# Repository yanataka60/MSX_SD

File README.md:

# MSXにSD-CARDからロード、セーブ機能

　MSX、MSX2、MSX2+、MSXturboRでSD-CARDからロード、セーブ機能を実現するものです。

　ROM-BASIC、DISK-BASICのどちらからも使えますが、DISK-BASICのフリーエリアでは動かないカセット用プログラム(ゲーム)もあります。

　FDD内蔵機種でフリーエリアが足りない場合は、SHIFTキーを押しながら電源投入又はリセットしてFDDを切り離してください。

　CMTからの読み込み実行に数分掛かっていたゲームも数十秒で実行できます。

　なお、Arduino、ROMへ書き込むための機器が別途必要となります。

## 対応できないもの
　BASICにSD専用命令を追加することでSD-CARDへのアクセスを実現しています。

　機械語からBIOSをコール、又は独自ルーチンでCMTからLOADするソフトには対応していません。

　雑誌打ち込み系のLOAD、SAVEを想定しています。市販ソフトはLOAD出来ればラッキーくらいに思って活用してください。

## 参考
　市販ソフトをcasファイル化した時に多段ロードではない単純にBASICプログラム、機械語プログラムをロードするものは大丈夫だと思います。

　また、２段ロードでも最初のBASICプログラム中から2段目の機械語プログラムを「BLOAD」で呼び出すものは「CALL SBLOAD」又は「CALL SBLOAD(,R)」に置き換えることで対応できると思います。

## 回路図
　KiCadフォルダ内のMSX_SD.pdfを参照してください。

[回路図](https://github.com/yanataka60/MSX_SD/blob/main/Kicad/MSX_SD.pdf)

## 部品
|番号|品名|数量|備考|
| ------------ | ------------ | ------------ | ------------ |
||J2、J3のいずれか(注1)|||
|J2|Micro_SD_Card_Kit|1|秋月電子通商 AE-microSD-LLCNV (注2)|
|J3|MicroSD Card Adapter|1|Arduino等に使われる5V電源に対応したもの (注4)|
|D1|1N4148|1||
|U1|74LS02|1||
|U2|74LS138|1||
|U3|27256相当品|1|29C256は可、28C256は不可|
|U4|8255|1||
|U5|Arduino_Pro_Mini_5V|1|Atmega328版を使用 168版は不可。(注3)|
|C1～C4|積層セラミックコンデンサ 0.1uF|4||
|C5|電解コンデンサ 16v100uF|1||
||ピンヘッダ|2Pin分|Arduino_Pro_MiniにはA4、A5用のピンヘッダが付いていないため別途調達が必要です 秋月電子通商 PH-1x40SGなど|
||ピンソケット(任意)|26Pin分|Arduino_Pro_Miniを取り外し可能としたい場合に調達します 秋月電子通商 FHU-1x42SGなど|

　　　注1)J2又はJ3のどちらかを選択して取り付けてください。

　　　注2)秋月電子通商　AE-microSD-LLCNVのJ1ジャンパはショートしてください。

　　　注3)Arduino Pro MiniはA4、A5ピンも使っています。

　　　注4)MicroSD Card Adapterを使う場合

　　　　　J3に取り付けます。

　　　　　MicroSD Card Adapterについているピンヘッダを除去してハンダ付けするのが一番確実ですが、J3の穴にMicroSD Card Adapterをぴったりと押しつけ、裏から多めにハンダを流し込むことでハンダ付けをする方法もあります。なお、この方法の時にはしっかりハンダ付けが出来たかテスターで導通を確認しておいた方が安心です。

## ROMへの書込み
　Z80フォルダ内のEXT_ROM.binをROMライター(TL866II Plus等)を使って27256又は29C256に書き込みます。

## Arduinoプログラム
　Arduino IDEを使ってArduinoフォルダのMSX_SDフォルダ内MSX_SD.inoを書き込みます。

　SdFatライブラリを使用しているのでArduino IDEメニューのライブラリの管理からライブラリマネージャを立ち上げて「SdFat」をインストールしてください。

　「SdFat」で検索すれば見つかります。「SdFat」と「SdFat - Adafruit Fork」が見つかりますが「SdFat」のほうを使っています。

## 接続
　カートリッジスロットに挿入します。

### SD-CARD
　出来れば8GB以下のSDカードを用意してください。

　ArduinoのSdFatライブラリは、SD規格(最大2GB)、SDHC規格(2GB～32GB)に対応していますが、SDXC規格(32GB～2TB)には対応していません。

　また、SDHC規格のSDカードであっても32GB、16GBは相性により動作しないものがあるようです。

　FAT16又はFAT32が認識できます。NTFSは認識できません。

　ルートに置かれた拡張子が「.CAS」形式ファイルのみ認識できます。(以外のファイル、フォルダも表示されますがLOAD実行の対象になりません)

　ファイル名は拡張子を除いて32文字まで、ただし半角カタカナ、及び一部の記号はArduinoが認識しないので使えません。パソコンでファイル名を付けるときはアルファベット、数字および空白でファイル名をつけてください。

## 使い方
　BASICから以下のコマンドが使えます。

　各コマンドでパラメータを指定する場合には必ず"("をつけてください。"("が無い場合には、MSXの仕様により入力した文字列のすべてがコマンド名として解釈されるため、パラメータを指定しなかったことになります。

### ○CALL SDIR[CR] 又は CALL SDIR("文字列")[CR]
### 【省略形】_SDIR[CR] 又は _SDIR("文字列")[CR]

文字列を指定するときは必ず"("をつけてください。後ろの")"は有っても無くても構いません。

ダブルコーテーションは有っても無くても構いません。

文字列を入力せずにSDIR[CR]のみ入力するとSD-CARDルートディレクトリにあるファイルの一覧を表示します。

文字列を付けて入力すればSD-CARDルートディレクトリにあるその文字列から始まるファイルの一覧を表示します。

10件表示したところで指示待ちになるので打ち切るならESCを入力すると打ち切られ、Bキーで前の10件に戻ります。それ以外のキーで次の10件を表示します。

　行頭に0から9の数字を付加して表示してあるのでSETLしたいファイルの頭についている数字を入力するとSETLコマンドが実行されます。

　表示される順番は、登録順となりファイル名アルファベッド順などのソートした順で表示することはできません。

#### 例)
　　CALL SDIR[CR]

　　CALL SDIR("P")[CR]

　　CALL SDIR(P)[CR]

### ○CALL SETL("DOSファイル名")[CR]
### 【省略形】_SETL("DOSファイル名")[CR]
指定したDOSファイル名のファイルをSD-CARDからLOAD出来るようにセットします。ファイル名の前には必ず"("をつけてください。後ろの")"は有っても無くても構いません。

ダブルコーテーションは有っても無くても構いません。

ファイル名の最後の「.cas」は有っても無くても構いません。

SETLを実行することでカセットテープをセットして読み込む準備をしたことになります。

#### 例)
　　CALL SETL("TEST")[CR]

### ○CALL SLOAD[CR] 又は CALL SLOAD("ファイル名")[CR]
### 【省略形】_SLOAD[CR] 又は _SLOAD("ファイル名")[CR]
CALL SDIR又はCALL SETLでセットしたDOSファイル名に記録されているBASICプログラムをロードします。

ファイル名の前には必ず"("をつけてください。

ダブルコーテーションは有っても無くても構いません。

ファイルデスクリプタ「CAS0:」は不要です。

ASCII形式のBASICプログラムには対応していません。

Rオプションには対応していません。LOAD後実行したい場合にはマルチステートメントでRUNを付け加え、CALL SLOAD:RUN[CR]又はCALL SLOAD("ファイル名"):RUN[CR]などとしてください。

ファイル名が指定されていなければ最初に見つけたBASICプログラムから、ファイル名を指定していれば入力したファイル名から始まるBASICプログラムが見つかるとロードが始まります。

#### 例)
　　CALL SLOAD[CR]

　　CALL SLOAD("TEST")[CR]

カセットテープと同じようにSLOAD命令等で読み込みが行われる度にDOSファイル名で指定したファイルに保存されているプログラムが先頭から一つずつ読み込まれます。

カセットデッキのように巻き戻しは無いので戻りたい時にはもう一度CALL SDIR又はCALL SETLコマンドを実行すれば先頭のプログラム又はデータに戻ります。

### ○CALL SBLOAD[CR]、CALL SBLOAD ("ファイル名")[CR]、CALL SBLOAD(,R)[CR] 又は CALL SBLOAD ("ファイル名",R)[CR]
### 【省略形】_SBLOAD[CR]、_SBLOAD ("ファイル名")[CR]、_SBLOAD(,R)[CR] 又は _SBLOAD ("ファイル名",R)[CR]
CALL SDIR又はCALL SETLでセットしたDOSファイル名に記録されている機械語プログラムをロードします。

ファイル名の前には必ず"("をつけてください。

ダブルコーテーションは有っても無くても構いません。

ファイルデスクリプタ「CAS0:」は不要です。

RオプションをつけることでLOAD後指定された実行開始アドレスから直ちに実行されます。

ファイル名が指定されていなければ最初に見つけた機械語プログラムから、ファイル名を指定していれば入力したファイル名から始まる機械語プログラムが見つかるとロードが始まります。

#### 例)
　　CALL SBLOAD[CR]

　　CALL SBLOAD("TEST")[CR]

　　CALL SBLOAD(,R)[CR]

　　CALL SBLOAD("TEST",R)[CR]

カセットテープと同じようにSBLOAD命令等で読み込みが行われる度にDOSファイル名で指定したファイルに保存されているプログラムが先頭から一つずつ読み込まれます。

カセットデッキのように巻き戻しは無いので戻りたい時にはもう一度CALL SDIR又はCALL SETLコマンドを実行すれば先頭のプログラム又はデータに戻ります。

### ○CALL SETS("DOSファイル名")[CR]
### 【省略形】_SETS("DOSファイル名")[CR]
SD-CARDへのSAVEが指定したDOSファイル名のファイルとなるようにセットします。ファイル名の前には必ず"("をつけてください。後ろの")"は有っても無くても構いません。

ダブルコーテーションは有っても無くても構いません。

ファイル名の最後の「.cas」は有っても無くても構いません。

指定したDOSファイル名のファイルがSD-CARDに存在しない場合は新たに作成され、存在する場合にはそのファイルの続きに追記されます。

SETSを実行することでカセットテープをセットして書き込む準備をしたことになります。

なお、SETSを実行せずにSSAVE、SBSAVEコマンドを実行すると「DEFAULT.cas」というDOSファイル名のファイルに自動的に書き込まれます。

「DEFAULT.cas」でなく好きなDOSファイル名のファイルに書き込みたい時には事前にSETSコマンドを実行してください。

#### 例)
　　CALL SETS("TEST")[CR]

### ○CALL SSAVE("ファイル名")[CR]
### 【省略形】_SSAVE("ファイル名")[CR]
CALL SETSでセットしたDOSファイル名のファイルにBASICプログラムをSAVEします。

ファイル名の前には必ず"("をつけてください。

ダブルコーテーションで必ず括る必要はありませんが、MSXの仕様上ダブルコーテーションで括った場合には文字列として判断され小文字はそのまま小文字ですが、括らなかった場合には変数名と判断され小文字はすべて大文字に変換されます。

ファイルデスクリプタ「CAS0:」は不要です。

ファイル名は省略できません。6文字以内でファイル名を指定してください。

#### 例)
　　CALL SSAVE("test")[CR]　　　:ファイル名testとしてSAVEされます。

　　CALL SSAVE("TEST")[CR]　　　:ファイル名TESTとしてSAVEされます。

　　CALL SSAVE(test)[CR]　　　　:ファイル名TESTとしてSAVEされます。

　　CALL SSAVE(TEST)[CR]　　　　:ファイル名TESTとしてSAVEされます。

カセットテープと同じようにSSAVE命令等で書き込みが行われる度にDOSファイル名で指定したファイルにBASICプログラムを追記します。

### ○CALL SBSAVE("ファイル名",開始アドレス,終了アドレス,実行開始アドレス)[CR]
### 【省略形】_SBSAVE("ファイル名",開始アドレス,終了アドレス,実行開始アドレス)[CR]
CALL SETSでセットしたDOSファイル名のファイルに開始アドレスから終了アドレスまでのメモリ上に置かれている機械語プログラムをSAVEします。

ファイル名の前には必ず"("をつけてください。

ダブルコーテーションで必ず括る必要はありませんが、MSXの仕様上ダブルコーテーションで括った場合には文字列として判断され小文字はそのまま小文字ですが、括らなかった場合には変数名と判断され小文字はすべて大文字に変換されます。

ファイルデスクリプタ「CAS0:」は不要です。

ファイル名、開始アドレス、終了アドレス、実行開始アドレスは16進数(&H)または32767までの10進数で指定してください。省略できません。

6文字以内でファイル名を指定してください。

#### 例)
　　CALL SBSAVE("TEST",&HA000,&HAFFF,&HA000)[CR]

カセットテープと同じようにSBSAVE命令等で書き込みが行われる度にDOSファイル名で指定したファイルに機械語プログラムを追記します。

### ○CALL DUMP[CR] 又は CALL DUMP(開始アドレス)[CR]
### 【省略形】_DUMP[CR] 又は _DUMP(開始アドレス)[CR]
メモリの内容を開始アドレスから128Byte分表示します。

開始アドレスを指定する場合には"("をつけ、16進数(&H)または32767までの10進数で指定してください。

開始アドレスを省略した場合には直前にCALL SBLOADされた機械語プログラムの実行開始アドレス又はCALL DUMPで表示された続きを表示します。

#### 例)
　　CALL DUMP(&HA000)[CR]　　　:アドレスA000からメモリ内容を表示します。

　　直後にCALL DUMP[CR]　　　　:直前に表示したメモリ内容(&HA000～&HA07F)の続きとして&HA080～&HA0FFを表示します。

　　CALL SBLOADを実行した直後にCALL DUMP[CR]　　　　:直前にLOADされた機械語プログラムの実行開始アドレスからメモリ内容を表示します。

### ○CALL EDIT[CR] 又は CALL EDIT(開始アドレス)[CR]
### 【省略形】_EDIT[CR] 又は _EDIT(開始アドレス)[CR]
開始アドレスが表示されるのでその後ろに16進数を入力し最後に[CR]を押すことでメモリにデータを書き込むことができます。

開始アドレスを指定する場合には"("をつけ、16進数(&H)または32767までの10進数で指定してください。

開始アドレスを省略した場合には直前にCALL SBLOADされた機械語プログラムの実行開始アドレス又はCALL DUMPで表示された続きのアドレスが書き込み開始アドレスとなります。

#### 例)
　　CALL EDIT(&HA000)[CR]　　　:とすると改行してA000が表示されるので16進数を入力後[CR]を押す。

　　A000 12 34 56 78 90[CR]　　:アドレスA000から 12 34 56 78 90の5Byteが書き込まれ、次のアドレスA005が表示される。

　　A005 [CR]　　　　　　　　　:終了したい時はアドレス表示の後に[CR]だけ押せば終了となる。

### ○CALL GOTO[CR] 又は CALL GOTO(実行開始アドレス)[CR]
### 【省略形】_GOTO[CR] 又は _GOTO(実行開始アドレス)[CR]
実行開始アドレスの機械語プログラムを呼び出します。

開始アドレスを指定する場合には"("をつけ、16進数(&H)または32767までの10進数で指定してください。

開始アドレスを省略した場合には直前にCALL SBLOADされた機械語プログラムの実行開始アドレス又はCALL DUMPで表示された続きが実行開始アドレスとなります。

#### 例)
　　CALL GOTO(&HA000)[CR]　　　:アドレスA000からの機械語プログラムを呼び出します。

　　CALL SBLOADを実行した直後にCALL GOTO[CR]　　　:直前にLOADされた機械語プログラムの実行開始アドレスの機械語プログラムを呼び出します。CALL SBLOAD(,R)と同等の動作となります。

### 操作上の注意
　~~「SD-CARD INITIALIZE ERROR」と表示されたときは、SD-CARDが挿入されているか確認し、SD-CARDを挿入して再度実行してください。~~

　~~SD-CARDにアクセスしていない時に電源が入ったままで SD-CARDを抜いた後、再挿入しても動作します。もし、「SD-CARD INITIALIZE ERROR」となる場合には本体の電源を入れ直してください。~~

　(2024.3.13) SD-CARDにアクセスしていない時に電源が入ったままでSD-CARDを抜くと再度SD-CARDを挿入してもSD-CARDにアクセスできない問題を解消しました。(Arduinoを最新版に書き換えてください)

　再度SD-CARDを挿入した後、_SDIR、_SETL、_SETS、_SSAVE、_SBSAVE等でSD-CARDに3回ほどアクセスすれば復旧します。

　_SLOAD、_SBLOADでも復旧しますが、_SDIR、_SETL等DOSファイル名をセットするところから復旧させることをお勧めします。

## 機械語多段ロードでBIOSをコールしているプログラムへの対応【テストバージョン】
　「MSX快速マシン語ゲーム集」に掲載されている「ジグソーセット」は、選んだ絵のデータを機械語のサブプログラムからBIOSのCMTアクセスルーチンをコールしてロードする仕様になっています。

　CALL文で拡張したSDアクセス用のコマンドではBIOSを直接コールするアプリケーションには対応できないのでアプリケーション中のCMT用BIOSコール部分を書き換えてSDアクセスする実験をしてみました。

　今回は、BIOSのCMTロード関連のみパッチを当てています。BIOSのCMTセーブ関連は未対応です。

　同様に、機械語多段ロードでBIOSをコールしているゲーム等ももしかしたら起動できるかもしれません。

#### 注意
　アプリケーションからSDアクセスルーチンをコールするためにSDアクセスルーチンをFDのワークエリアにコピーしています。機械語多段ロードでBIOSをコールしているプログラムをテストするときは必ずFDを切り離して起動してください。

　機械語多段ロードでBIOSをコールしているプログラムをロード実行しない限りFDとは共存します。

　なお、機械語多段ロードのアプリケーションでもBIOSのCMT関連ルーチンをコールせず、独自の特殊フォーマットでCMTから読み込んでいるものは対処しようがないので読み込めません。

### ROMへの書込み
　BIOS CALL REPLACE TESTフォルダ内Z80フォルダ内のEXT_ROM.binをROMライター(TL866II Plus等)を使って27256又は29C256に書き込みます。

　同ファイルにあるEXT_ROM2.sはアセンブル後のコードをEXT_ROM.binに含めてあります。

　テスト用のプログラムを付け加えた以外は通常版と同じですのでテストを止めたとしても元に戻す必要はありません。

### Arduinoプログラム
　Arduino IDEを使ってBIOS CALL REPLACE TESTフォルダ内ArduinoフォルダのMSX_SDフォルダ内MSX_SD.inoを書き込みます。

　テスト用のプログラムを付け加えた以外は通常版と同じですのでテストを止めたとしても元に戻す必要はありません。

### アプリケーションパッチあてWindows用ツール
　デスクトップ等適当な場所にBIOS CALL REPLACE TESTフォルダ内の「CAS2SD_CHECK.exe」をコピーしてダブルクリックで起動させてください。

　次にSD用パッチを当てたいCASファイルをCAS2SD_CHECKにドラッグアンドドロップしてください。

　ドロップされたアプリケーションにBIOSのCMT関連ルーチンを呼び出していると思われるコードが発見された場合は、元のCASファイルと同じフォルダに元のCASファイルのファイルネームに「_SD」を付加したCASファイルと変更箇所を保存したTXTファイルを作成します。

　ドロップされたアプリケーションにBIOSのCMT関連ルーチンを呼び出していると思われるコードが無い場合には、何も作成されません。

例)

　「JIGSAW SET.cas」をドラッグアンドドロップ

　　JIGSAW SET_SD.cas、JIGSAW SET_SD.txtが作成される。

### レトロPC用ビットマップコンバーター TINY Bitmap Converterで生成された画像のロード
　TINY野郎さんのTINY Bitmap Converterで作られたCASファイルをMSX_SDで読み込むためのパッチ当てプログラムを作ってみました。

　デスクトップ等適当な場所にBIOS CALL REPLACE TESTフォルダ内の「TINYBMPCONV_MSX_SD_CONV.exe」をコピーしてダブルクリックで起動させてください。

　次にSD用パッチを当てたいCASファイルをTINYBMPCONV_MSX_SD_CONVにドラッグアンドドロップしてください。

　ドロップされた元のCASファイルと同じフォルダに元のCASファイルのファイルネームに「_SD」を付加したCASファイルを作成します。

　TINY Bitmap ConverterでMSX用に生成されたCASファイル以外をドロップしても多分何も作成されません。

例)

　「GAZOU.cas」をドラッグアンドドロップ

　　GAZOU_SD.casが作成される。

#### やっていること
　TINY Bitmap ConverterでMSX用に生成されたCASファイルはBASICで書かれたローダーの後ろに画像データがあります。

　BASICで書かれたローダーはDATA文で読み込んだ機械語をメモリに書き込んで実行していますが、DATA文なのでCAS2SD_CHECKを使ってもMSX_SD用にパッチ当てが出来ません。

　そこでDATA文に書かれたCMTルーチンコール用の機械語をSD用に置き換えています。

## 謝辞
　基板の作成に当たり以下のデータを使わせていただきました。ありがとうございます。

　Arduino Pro Mini

　　https://github.com/g200kg/kicad-lib-arduino

　AE-microSD-LLCNV

　　https://github.com/kuninet/PC-8001-SD-8kRAM

　にが様に多大なるご助言を頂きました。ありがとうございます。

## 追記
2023.5.22 キースキャンルーチンにWAITを追加

2023.5.28 _SBLOAD(,R)、_GOTOコマンドからのリターン時にHLレジスタを復帰していなかったバグを修正

　　　　_GOTOコマンドで実行開始アドレス省略時にマルチステートメントに対応していなかったバグを修正

　　　　マシン語自動実行用ワークエリア調整

2023.6.3 機械語多段ロードでBIOSをコールしているプログラムへの対応【テストバージョン】をアップした。

2023.8.2 ROMへの書込みにアドレス0000Hからで済むよう変更した。

2024.1.15 SDカードは8GB以下が望ましいことを追記。

2024.2.4 TINY Bitmap Converter用パッチ当てプログラムを作成。

2024.3.13 電源が入ったままでSD-CARDを抜くと再度SD-CARDを挿入してもSD-CARDにアクセスできない問題を解消した。

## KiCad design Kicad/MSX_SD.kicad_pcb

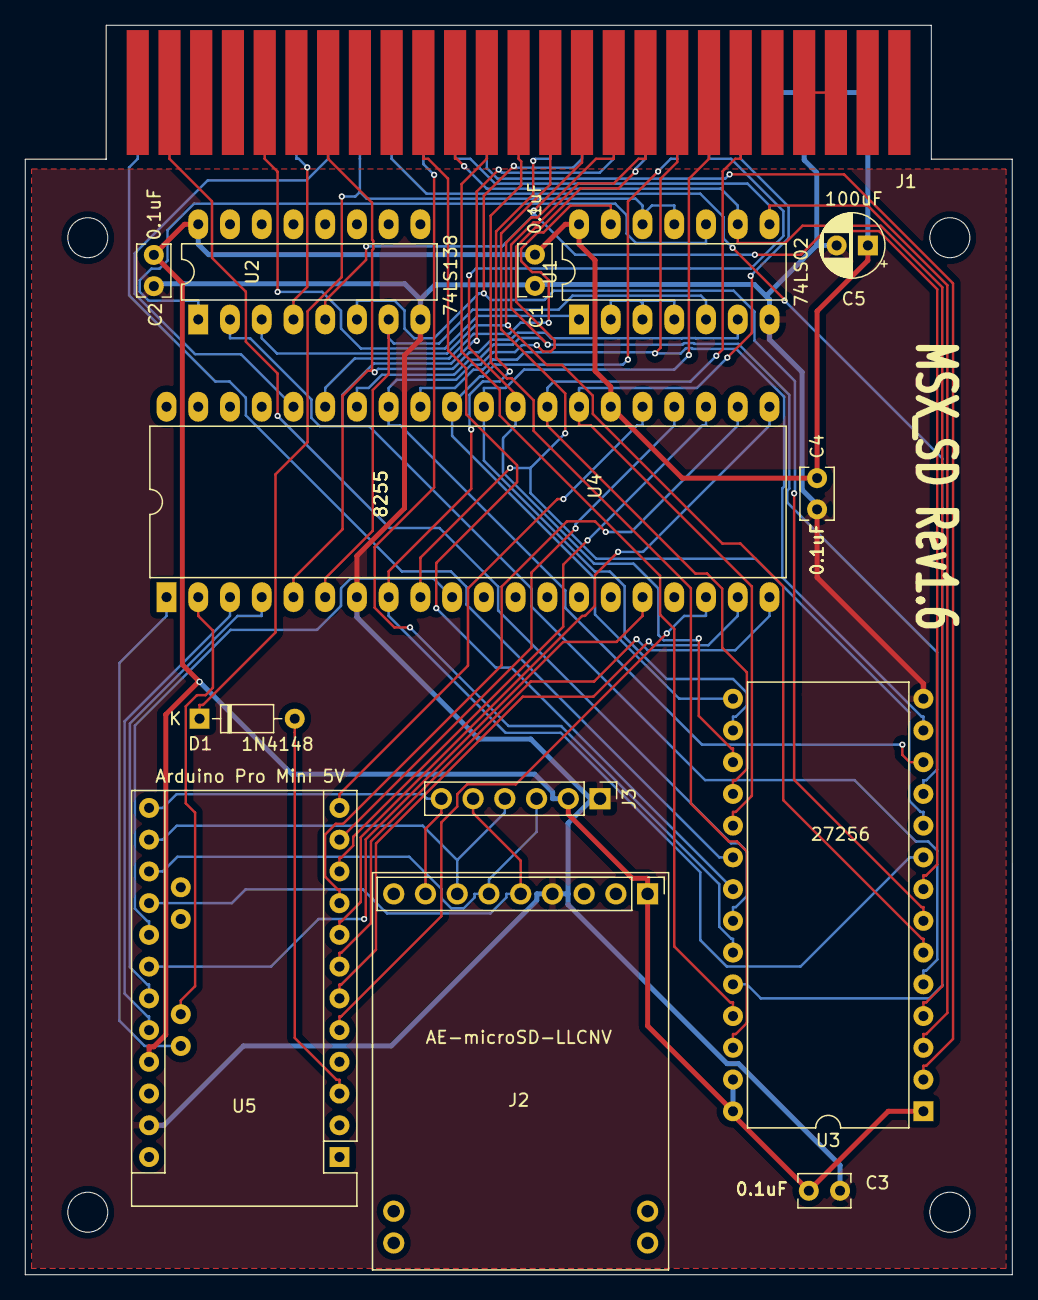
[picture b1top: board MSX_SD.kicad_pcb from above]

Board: 2 copper layers, 79.0 x 100.0 mm, 18 parts (0 on the bottom side), 55 nets.

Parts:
C1, C2, C3, C4: 0.1uF; C_Rect_L4.0mm_W2.5mm_P2.50mm
C5: 100uF; CP_Radial_D5.0mm_P2.50mm
D1: 1N4148; D_DO-35_SOD27_P7.62mm_Horizontal
J1: MSX BUS; BUS_50Pin
J2: Micro_SD_Card_Kit; AE-microSD-LLCNV
J3: MicroSD Card Adapter; PinHeader_1x06_P2.54mm_Vertical
MH1, MH2, MH3, MH4: MountingHole_3.2mm_M3
U1: 74LS02; DIP-14_W7.62mm_LongPads
U2: 74LS138; DIP-16_W7.62mm_LongPads
U3: 27256; DIP-28_W15.24mm
U4: 8255; DIP-40_W15.24mm_LongPads
U5: Arduino_Pro_Mini_5V; Arduino_Pro_Mini

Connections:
+5V: C1.2, C2.2, C3.1, C4.1, C5.1, J1.45, J1.47, J2.1, J3.2, U1.14, U2.16, U3.1, U3.27, U3.28, U4.26, U5.21
/A0: J1.28, U3.10, U4.9
/A1: J1.27, U3.9, U4.8
/A2: J1.30, U2.5, U3.8
/A3: J1.29, U2.6, U3.7
/A4: J1.32, U2.3, U3.6
/A5: J1.31, U2.2, U3.5
/A6: J1.22, U1.9, U3.4
/A7: J1.21, U1.8, U3.3
/A8: J1.24, U3.25
/A9: J1.17, U3.24
/A10: J1.20, U3.21
/A11: J1.19, U3.23
/A12: J1.23, U3.2
/A13: J1.26, U3.26
/CS: J2.8, J3.6, U5.13
/D0: J1.34, U3.11, U4.34
/D1: J1.33, U3.12, U4.33
/D2: J1.36, U3.13, U4.32
/D3: J1.35, U3.15, U4.31
/D4: J1.38, U3.16, U4.30
/D5: J1.37, U3.17, U4.29
/D6: J1.40, U3.18, U4.28
/D7: J1.39, U3.19, U4.27
/MISO: J2.6, J3.3, U5.15
/MOSI: J2.7, J3.4, U5.14
/SCK: J2.5, J3.5, U5.16
/SW1: J1.44, J1.46
/~BUSDIR: J1.10, U1.1
/~CS1: J1.1, U3.20
/~IORQ: J1.11, U2.4
/~RD: J1.14, U1.6, U4.5
/~RESET: D1.1, J1.15, U1.11, U1.12
/~SLTSL: J1.4, U3.22
/~WR: J1.13, U4.36
GND: C1.1, C2.1, C3.2, C4.2, C5.2, J1.41, J1.43, J2.4, J3.1, U1.7, U2.8, U3.14, U4.7, U5.23
unnamed: D1.2, U5.3
unnamed: U1.2, U1.3, U1.4
unnamed: U1.5, U2.7, U4.6
unnamed: U1.10, U2.1
unnamed: U1.13, U4.35
unnamed: U4.1, U5.A5
unnamed: U4.2, U5.A4
unnamed: U4.3, U5.20
unnamed: U4.4, U5.19
unnamed: U4.10, U5.17
unnamed: U4.16, U5.18
unnamed: U4.18, U5.5
unnamed: U4.19, U5.6
unnamed: U4.20, U5.7
unnamed: U4.21, U5.8
unnamed: U4.22, U5.9
unnamed: U4.23, U5.10
unnamed: U4.24, U5.11
unnamed: U4.25, U5.12
